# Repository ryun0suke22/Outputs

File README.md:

# Overview
このリポジトリは、過去の制作物をまとめたものになります。

- COSCO7_RNN: RNN(リカレントニューラルネット)の動作原理を調べ、まとめたもの。
- droneXAR: ドローンにとりつけたカメラから得た映像に、ARのエフェクトを組み合わせたもの。
- GraduateThesis: 会津大学学部四年時の卒業論文
- IEEE: CNNアルゴリズムを組み込み用途向けに最適化する手法の研究論文
- IoTDevice_DrawsyDetector: 入眠予兆検知デバイスを作成したプロジェクト
- MasterThesis: 会津大学大学院修士二年時の修士論文
- postcodeRecognizer: 畳こみニューラルネットでの文字認識アルゴリズムで、郵便番号認識をするアプリ
- ZYBO_RealTimeTMDSImageProcess: FPGA(Field Programmable Gate Array)を用いて、HDMI/VGAケーブルを通して入力される映像データに対して画像処理アルゴリズムを施すシステム

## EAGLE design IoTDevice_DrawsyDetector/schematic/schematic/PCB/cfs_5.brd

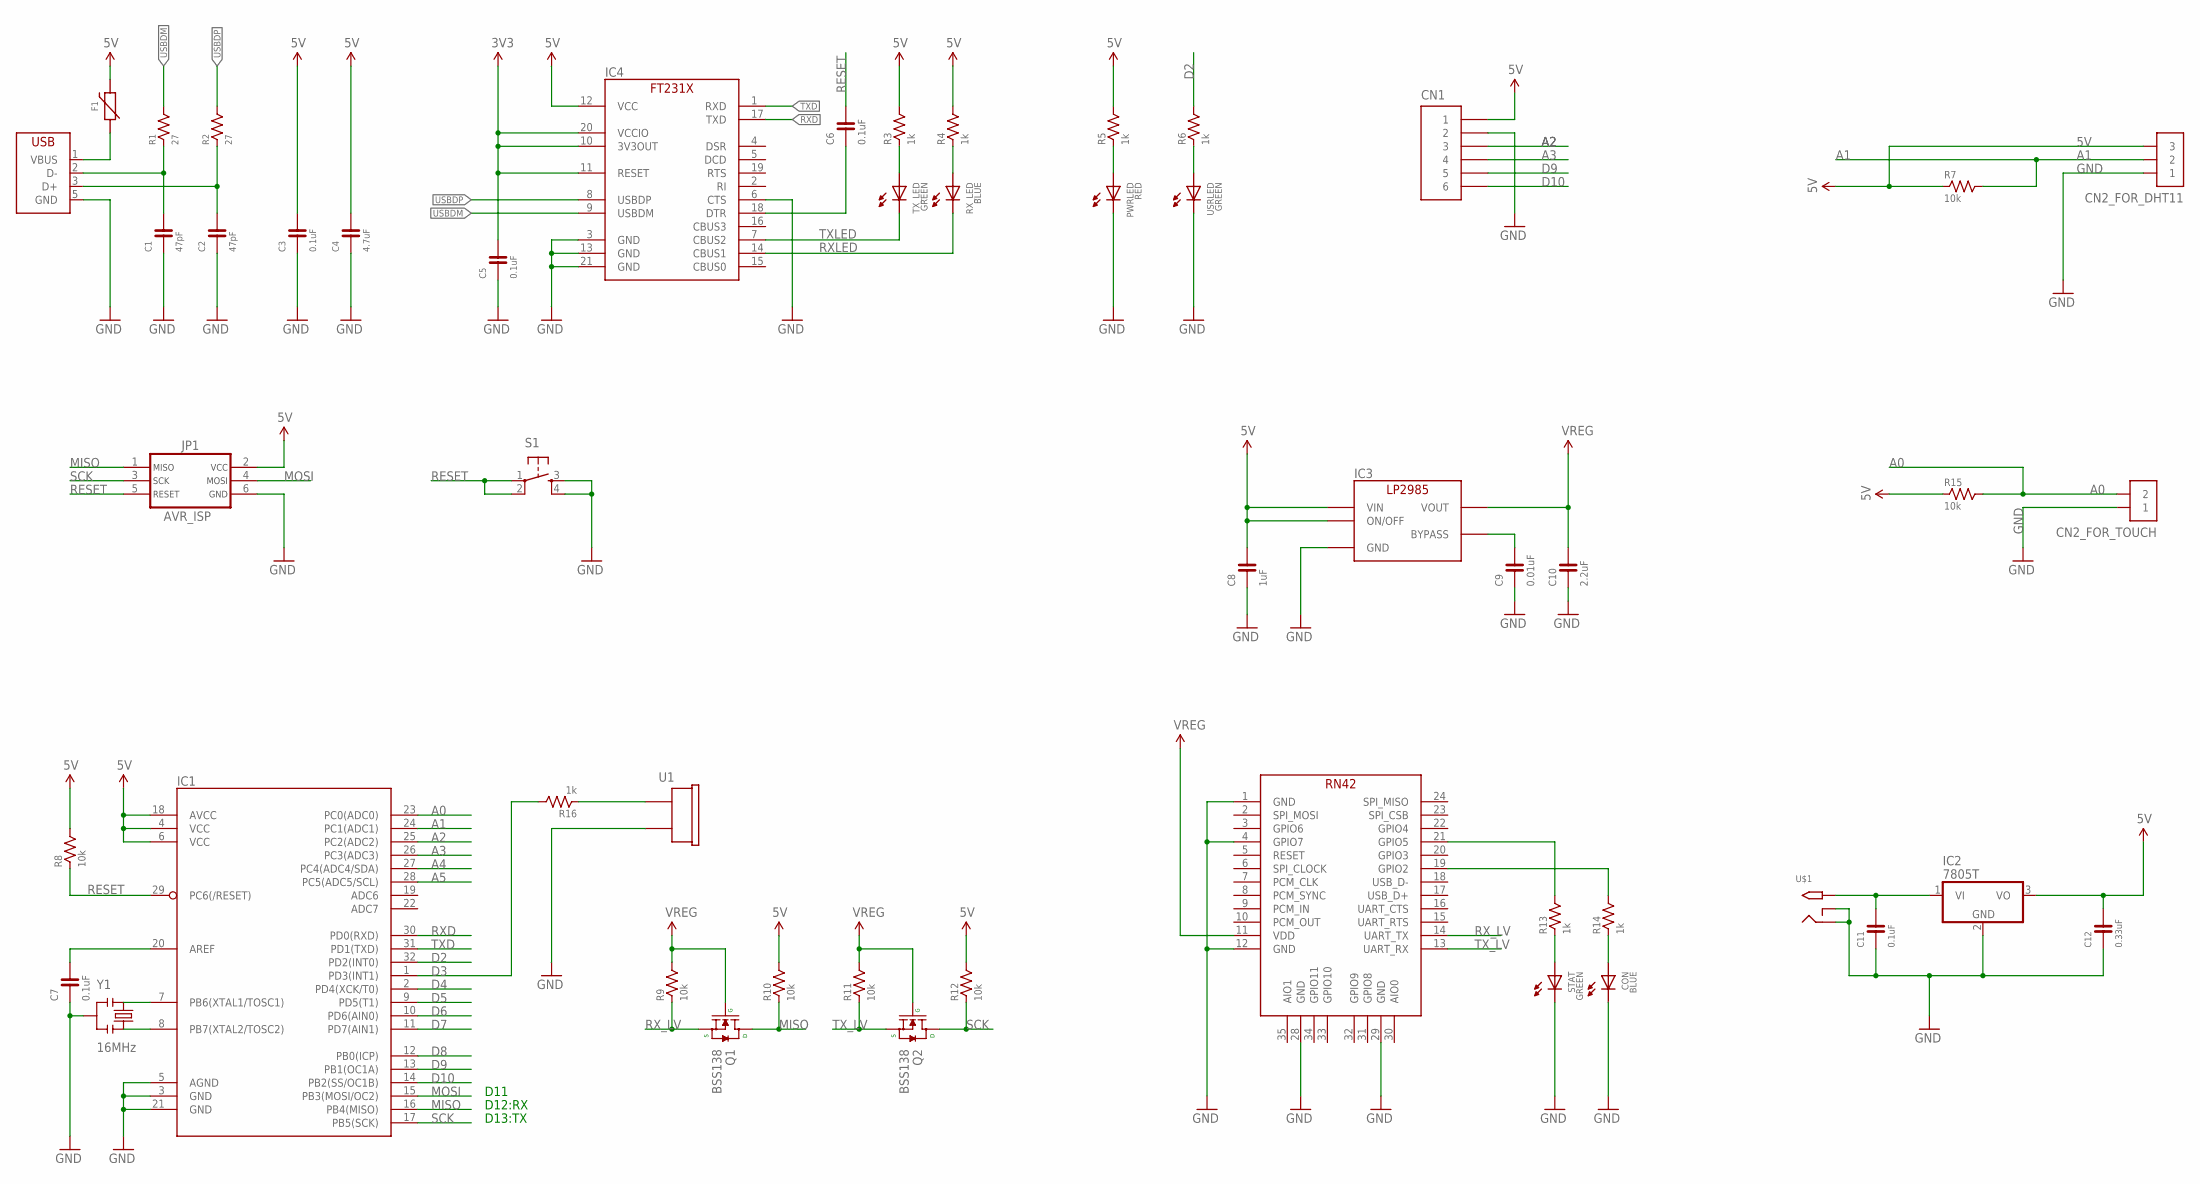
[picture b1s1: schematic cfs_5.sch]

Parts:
C1, C2: 47pF; EIA0603
C3, C5, C11: 0.1uF; EIA0603
C4: 4.7uF; EIA0603
C6, C7: 0.1uF; 0603
C8: 1uF; 0603
C9: 0.01uF; 0603
C10: 2.2uF; 0603
C12: 0.33uF; EIA0603
CN1: PIN_HEADER_1X6; PIN_1X6
CN2_FOR_DHT11: PIN_HEADER_1X3; PIN_1X3
CN2_FOR_TOUCH: PIN_HEADER_1X2; PIN_1X2
CON: BLUE; 0603
F1: FUSE-NANO; NANOSMDC035F
IC1: ATMEGA328P-AU; TQFP-32
IC2: 7805T; TO220H
IC3: LP2985-33DBV; SOT-23-5
IC4: FT231XQ; QFN-20_FT231X
JP1: AVR_ISP; TC2030
PWRLED: RED; 0603
Q1, Q2: BSS138; SOT23-3
R1, R2: 27; EIA0603
R3, R4, R5, R6, R13, R14, R16: 1k; 0603
R7, R8, R9, R10, R11, R12, R15: 10k; 0603
RX_LED: BLUE; 0603
S1: TACT-SWITCH-SMD_KMR2; KMR2
STAT: GREEN; 0603
TX_LED: GREEN; 0603
U1: BUZZER; PKM13EPYH4000-A0
U$1: 2.1MMJACKTHM; PJ-102A
U$4: MICROCHIP-RN42
USB1: USB-MICRO_B_SMT_HIROSE; ZX62R-B-5P
USRLED: GREEN; 0603
Y1: 16MHz; CSTCE_V

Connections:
3V3: C5.2, IC4.10 (3V3OUT), IC4.11 (RESET), IC4.20 (VCCIO)
5V: C3.2, C4.2, C8.2, C12.2, CN1.1, CN2_FOR_DHT11.3, F1.2, IC1.4 (VCC), IC1.6 (VCC), IC1.18 (AVCC), IC2.3 (VO), IC3.1 (VIN), IC3.3 (ON/OFF), IC4.12 (VCC), JP1.2, R3.2, R4.2, R5.2, R7.1, R8.2, R10.2, R12.2, R15.1
A0: CN2_FOR_TOUCH.2, IC1.23 (PC0(ADC0)), R15.2
A1: CN2_FOR_DHT11.2, IC1.24 (PC1(ADC1)), R7.2
A2: CN1.3, IC1.25 (PC2(ADC2))
A3: CN1.4, IC1.26 (PC3(ADC3))
A4: IC1.27 (PC4(ADC4/SDA))
A5: IC1.28 (PC5(ADC5/SCL))
D2: IC1.32 (PD2(INT0)), R6.2
D3: IC1.1 (PD3(INT1)), R16.2
D4: IC1.2 (PD4(XCK/T0))
D5: IC1.9 (PD5(T1))
D6: IC1.10 (PD6(AIN0))
D7: IC1.11 (PD7(AIN1))
D8: IC1.12 (PB0(ICP))
D9: CN1.5, IC1.13 (PB1(OC1A))
D10: CN1.6, IC1.14 (PB2(SS/OC1B))
DM: C2.2, R2.1, USB1.3 (D+)
DP: C1.2, R1.1, USB1.2 (D-)
DTR: C6.1, IC4.18 (DTR)
GND: C1.1, C2.1, C3.1, C4.1, C5.1, C7.1, C8.1, C9.1, C10.1, C11.1, C12.1, CN1.2, CN2_FOR_DHT11.1, CN2_FOR_TOUCH.1, CON.CATHODE, IC1.3 (GND), IC1.5 (AGND), IC1.21 (GND), IC2.2 (GND), IC3.2 (GND), IC4.3 (GND), IC4.6 (CTS), IC4.13 (GND), IC4.21 (GND), JP1.6, PWRLED.CATHODE, S1.3, S1.4, STAT.CATHODE, U1.2, U$1.RING, U$1.RING_SW, U$4.1 (GND), U$4.4 (GPIO7), U$4.12 (GND), U$4.28 (GND), U$4.29 (GND), USB1.5 (GND), USRLED.CATHODE, Y1.2
MISO: IC1.16 (PB4(MISO)), JP1.1, Q1.3 (D), R10.1
MOSI: IC1.15 (PB3(MOSI/OC2)), JP1.4
unnamed: R3.1, TX_LED.ANODE
unnamed: C7.2, IC1.20 (AREF)
unnamed: IC1.8 (PB7(XTAL2/TOSC2)), Y1.3
unnamed: IC1.7 (PB6(XTAL1/TOSC1)), Y1.1
unnamed: C9.2, IC3.4 (BYPASS)
unnamed: F1.1, USB1.1 (VBUS)
unnamed: R4.1, RX_LED.ANODE
unnamed: R13.2, U$4.21 (GPIO5)
unnamed: R14.2, U$4.19 (GPIO2)
unnamed: R13.1, STAT.ANODE
unnamed: CON.ANODE, R14.1
unnamed: C11.2, IC2.1 (VI), U$1.TIP
unnamed: PWRLED.ANODE, R5.1
unnamed: R16.1, U1.1
unnamed: R6.1, USRLED.ANODE
RESET: C6.2, IC1.29 (PC6(/RESET)), JP1.5, R8.1, S1.1, S1.2
RXD: IC1.30 (PD0(RXD)), IC4.17 (TXD)
RXLED: IC4.14 (CBUS1), RX_LED.CATHODE
RX_LV: Q1.2 (S), R9.1, U$4.14 (UART_TX)
SCK: IC1.17 (PB5(SCK)), JP1.3, Q2.3 (D), R12.1
TXD: IC1.31 (PD1(TXD)), IC4.1 (RXD)
TXLED: IC4.7 (CBUS2), TX_LED.CATHODE
TX_LV: Q2.2 (S), R11.1, U$4.13 (UART_RX)
USBDM: IC4.9 (USBDM), R1.2
USBDP: IC4.8 (USBDP), R2.2
VREG: C10.2, IC3.5 (VOUT), Q1.1 (G), Q2.1 (G), R9.2, R11.2, U$4.11 (VDD)

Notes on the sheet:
D11
D12:RX
D13:TX

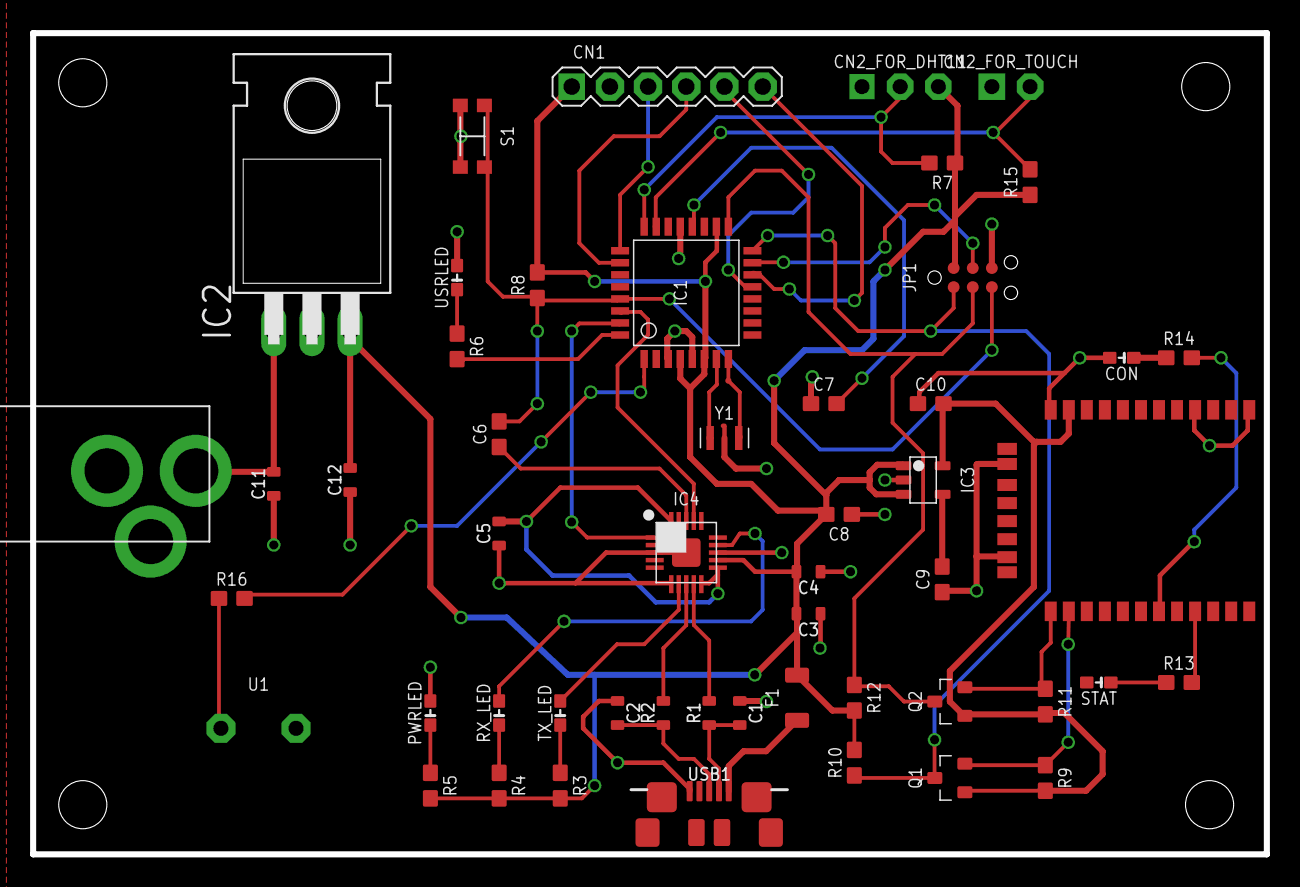
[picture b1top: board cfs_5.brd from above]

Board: 2 copper layers, 82.0 x 54.6 mm, 51 parts (0 on the bottom side), 42 nets.

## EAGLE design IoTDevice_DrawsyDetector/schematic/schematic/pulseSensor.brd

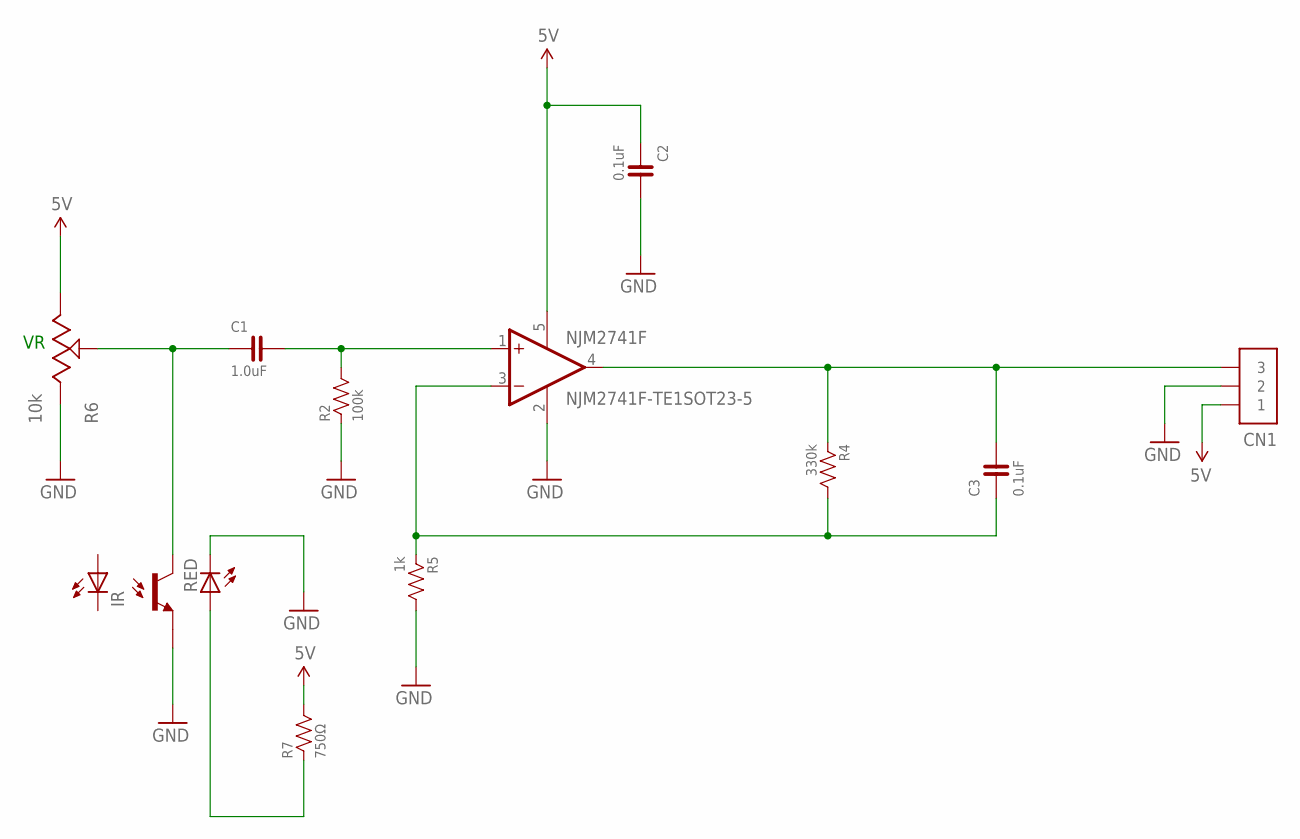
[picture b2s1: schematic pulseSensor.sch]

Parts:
C1: 1.0uF; 0603
C2, C3: 0.1uF; 0603
CN1: PIN_HEADER_1X3; PIN_1X3
NJL1: NJL5501R-TE1; NJL5501R-PAC
NJM2741F1: NJM2741F-TE1SOT23-5; NJL5501R-PAC
R2: 100k; 0603
R4: 330k; 0603
R5: 1k; 0603
R6: 10k; TC33X
R7: 750Ω; 0603

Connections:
5V: C2.1, CN1.1, NJM2741F1.5 (V+), R6.1, R7.2
GND: C2.2, CN1.2, NJL1.1, NJM2741F1.2 (GND), R2.1, R5.2, R6.3
unnamed: C3.2, CN1.3, NJM2741F1.4 (OUT), R4.1
unnamed: C1.1, NJL1.5, R6.2
unnamed: C3.1, NJM2741F1.3 (-IN), R4.2, R5.1
unnamed: NJL1.6, R7.1
unnamed: C1.2, NJM2741F1.1 (+IN), R2.2

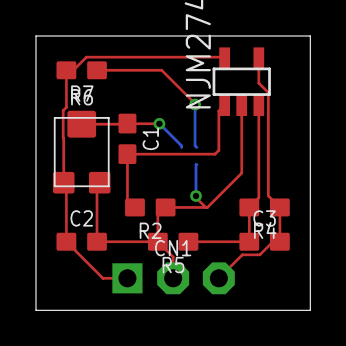
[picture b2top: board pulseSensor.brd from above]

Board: 2 copper layers, 15.2 x 15.2 mm, 11 parts (1 on the bottom side), 7 nets.

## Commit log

2020-04-07 add: first commit
2020-06-03 Organized.
2020-06-03 Added readMe
2020-06-03 add gradutate thesis slide.
2020-06-03 added soem refs.

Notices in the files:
parts and their libraries:
FaBo-Capacitor: Released under the Creative Commons Attribution-ShareAlike 4.0 License
https://creativecommons.org/licenses/by-sa/4.0
